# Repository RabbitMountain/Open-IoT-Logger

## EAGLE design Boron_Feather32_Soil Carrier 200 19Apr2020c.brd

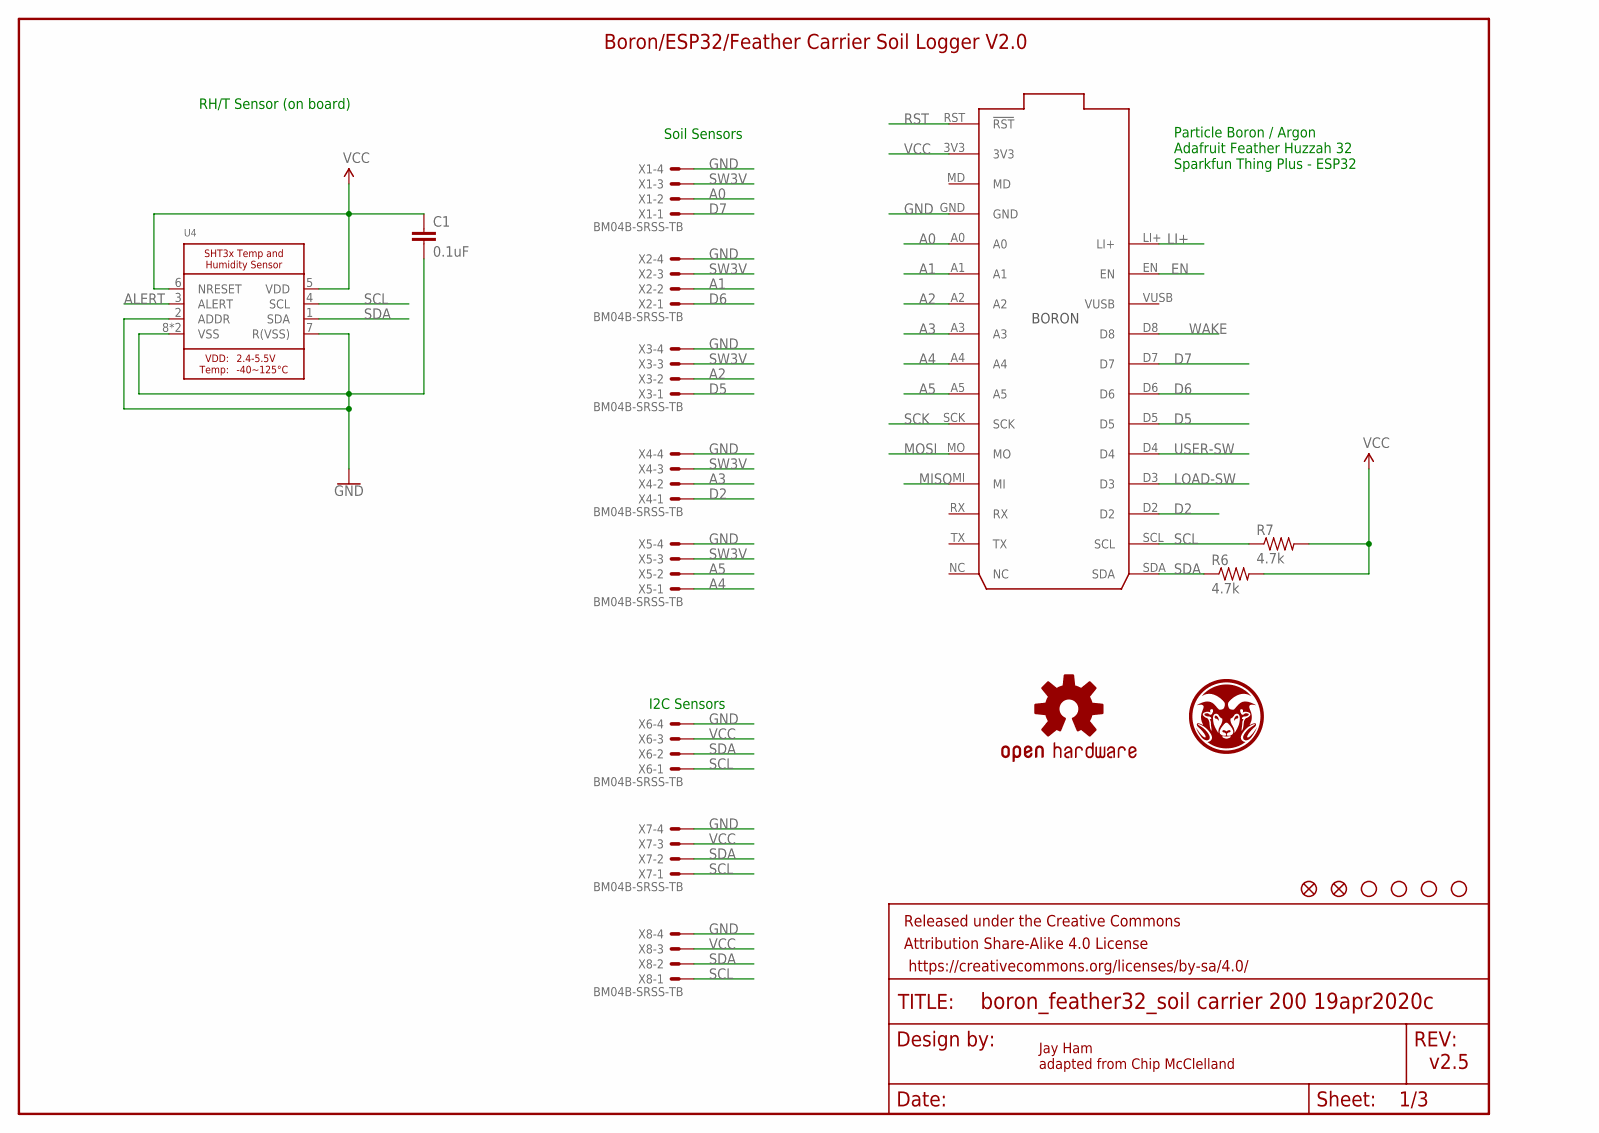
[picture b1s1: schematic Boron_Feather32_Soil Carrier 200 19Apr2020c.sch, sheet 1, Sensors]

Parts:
BORON: PARTICLE-DEVICES-BORON; PARTICLE-DEVICES_BORON
C1: 0.1uF; 0805
FD1, FD2: FIDUCIALUFIDUCIAL; FIDUCIAL-MICRO
FRAME1: FRAME-LETTER; CREATIVE_COMMONS
JP10, JP11, JP12, JP13: STAND-OFF
LOGO1: OSHW-LOGOM; OSHW-LOGO-M
R6, R7: 4.7k; 0805
U4: MICROBUILDER_SHT3X
U$1: CSU-RAM-LOGO7MM; CSU-RAM-7MM
X1, X2, X3, X4, X5, X6, X7, X8: BM04B-SRSS-TB

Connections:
A0: BORON.A0, X1.2
A1: BORON.A1, X2.2
A2: BORON.A2, X3.2
A3: BORON.A3, X4.2
A4: BORON.A4, X5.1
A5: BORON.A5, X5.2
ALERT: U4.3 (ALERT)
D2: BORON.D2, X4.1
D5: BORON.D5, X3.1
D6: BORON.D6, X2.1
D7: BORON.D7, X1.1
EN: BORON.EN; also elsewhere on the board
GND: BORON.GND, C1.2, U4.2 (ADDR), U4.7 (R(VSS)), U4.8 (VSS), U4.THERMAL (VSS), X1.4, X2.4, X3.4, X4.4, X5.4, X6.4, X7.4, X8.4; also elsewhere on the board
LI+: BORON.LI+; also elsewhere on the board
LOAD-SW: BORON.D3; also elsewhere on the board
MISO: BORON.MI
MOSI: BORON.MO
RST: BORON.RST (!RST); also elsewhere on the board
SCK: BORON.SCK
SCL: BORON.SCL, R7.1, U4.4 (SCL), X6.1, X7.1, X8.1; also elsewhere on the board
SDA: BORON.SDA, R6.1, U4.1 (SDA), X6.2, X7.2, X8.2; also elsewhere on the board
SW3V: X1.3, X2.3, X3.3, X4.3, X5.3; also elsewhere on the board
USER-SW: BORON.D4; also elsewhere on the board
VCC: BORON.3V3, C1.1, R6.2, R7.2, U4.5 (VDD), U4.6 (NRESET), X6.3, X7.3, X8.3; also elsewhere on the board
WAKE: BORON.D8; also elsewhere on the board

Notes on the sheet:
Jay Ham adapted from Chip McClelland
v2.5
Boron/ESP32/Feather Carrier Soil Logger V2.0
RH/T Sensor (on board)
I2C Sensors
Soil Sensors
Particle Boron / Argon Adafruit Feather Huzzah 32 Sparkfun Thing Plus - ESP32

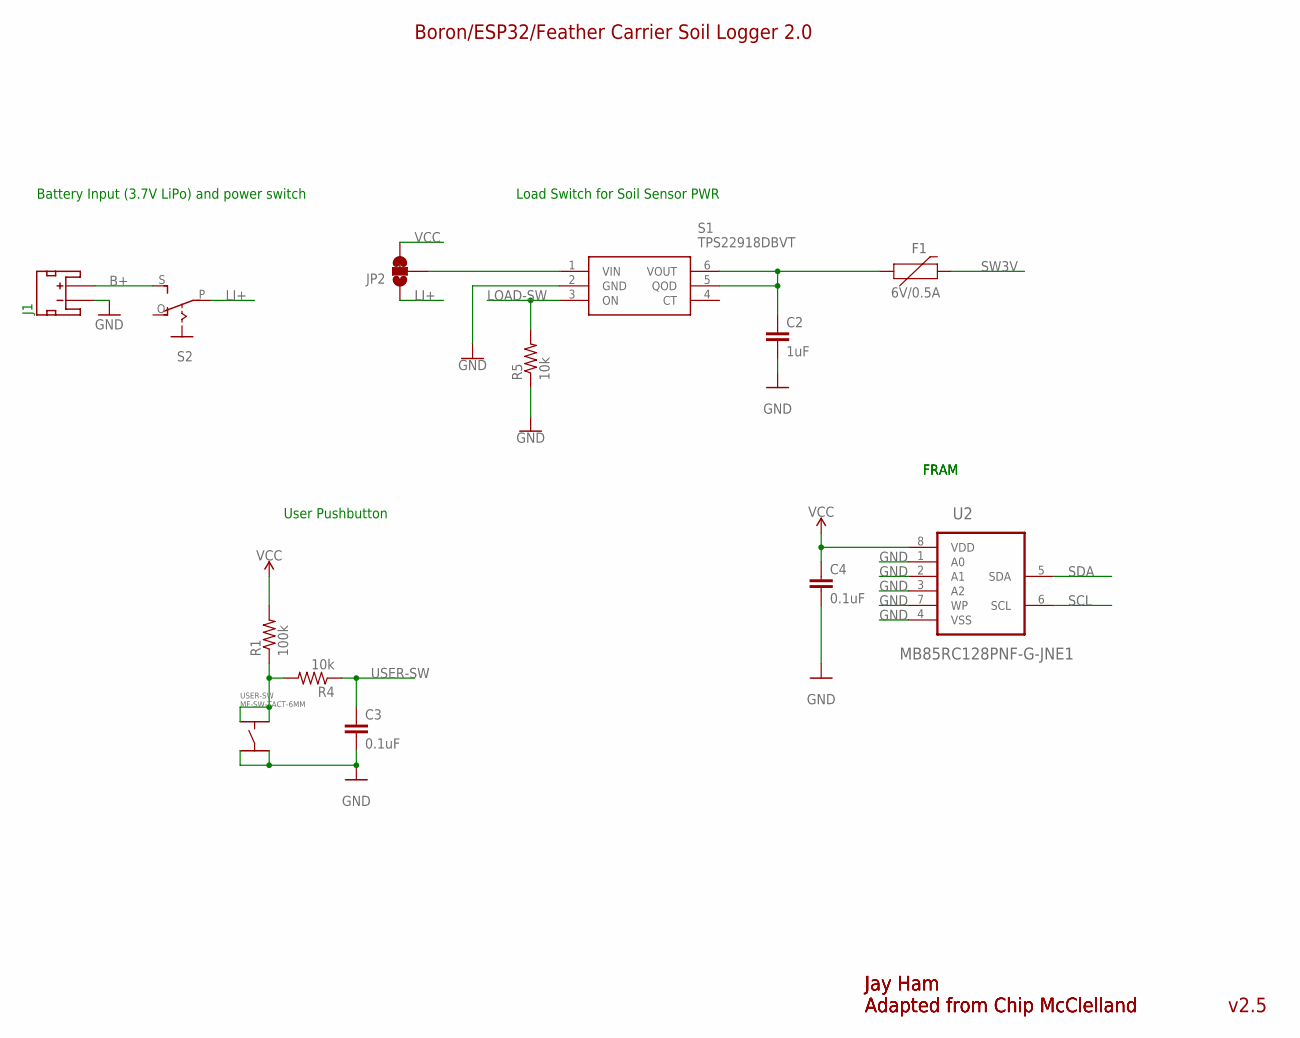
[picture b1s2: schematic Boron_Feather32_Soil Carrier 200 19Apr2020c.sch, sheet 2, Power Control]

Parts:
C2: 1uF; 0805
C3, C4: 0.1uF; 0805
F1: 6V/0.5A; 1206
J1: S2B-PH-SM4-TB(LF)(SN); JST-2-SMD
JP2: JUMPER-SMT_3_1-NC_TRACE_NO-SILK; SMT-JUMPER_3_1-NC_TRACE_NO-SILK
R1: 100k; 0805
R4, R5: 10k; 0805
S1: TPS22918DBVT; SOT95P280X145-6N
S2: EG1218S; EG1218
U2: MB85RC128PNF-G-JNE1; FUJITSU_BY_ELEMENT14_BATCH_1_SOIC127P600X175-8N
USER-SW: MF-SW-TACT-6MM; MF_SWITCHES_TACT6MM

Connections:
B+: J1.2 (+), S2.S; also elsewhere on the board
GND: C2.2, C3.2, C4.2, J1.1 (-), R5.1, S1.2 (GND), U2.1 (A0), U2.2 (A1), U2.3 (A2), U2.4 (VSS), U2.7 (WP), USER-SW.P$3, USER-SW.P$4; also elsewhere on the board
LI+: JP2.1, S2.P; also elsewhere on the board
LOAD-SW: R5.2, S1.3 (ON); also elsewhere on the board
unnamed: JP2.2, S1.1 (VIN)
unnamed: R1.1, R4.2, USER-SW.P$1, USER-SW.P$2
unnamed: C2.1, F1.1, S1.5 (QOD), S1.6 (VOUT)
SCL: U2.6 (SCL); also elsewhere on the board
SDA: U2.5 (SDA); also elsewhere on the board
SW3V: F1.2; also elsewhere on the board
USER-SW: C3.1, R4.1; also elsewhere on the board
VCC: C4.1, JP2.3, R1.2, U2.8 (VDD); also elsewhere on the board

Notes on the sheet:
Jay Ham Adapted from Chip McClelland
v2.5
Boron/ESP32/Feather Carrier Soil Logger 2.0
Load Switch for Soil Sensor PWR
Battery Input (3.7V LiPo) and power switch
FRAM
User Pushbutton

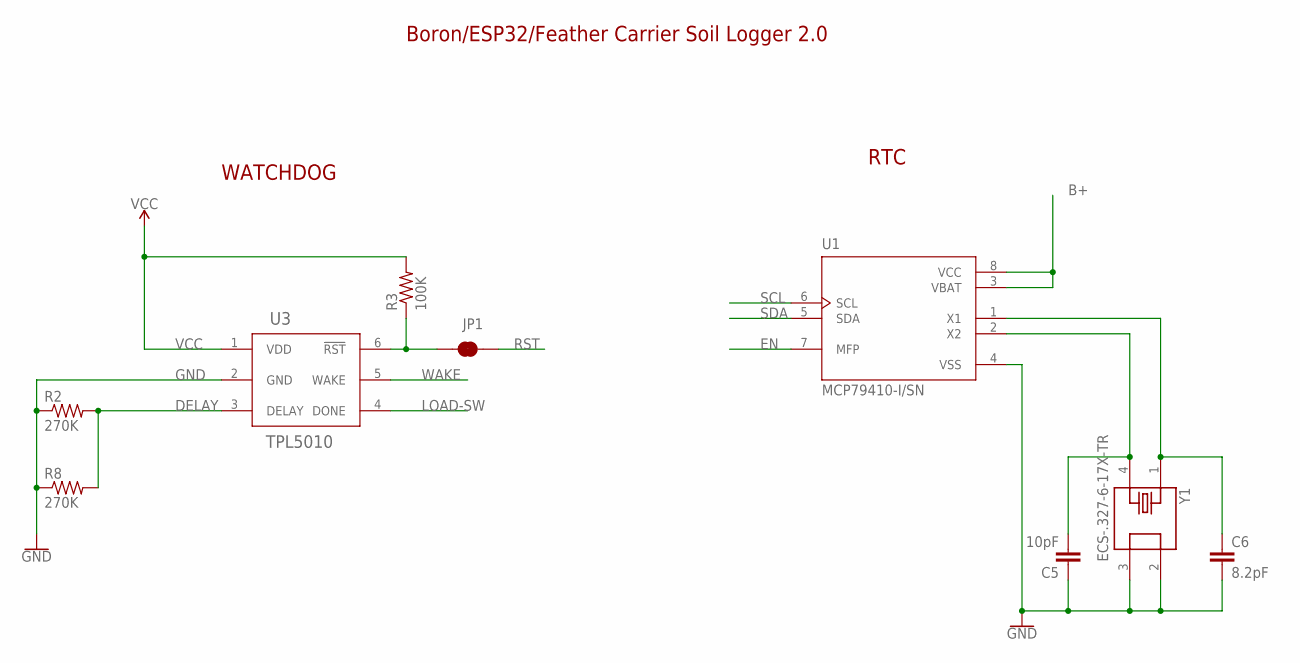
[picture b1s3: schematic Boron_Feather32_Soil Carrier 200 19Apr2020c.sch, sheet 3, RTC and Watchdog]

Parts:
C5: 10pF; SPARKFUN-CAPACITORS_0805$1
C6: 8.2pF; SPARKFUN-CAPACITORS_0805$1
JP1: JUMPER-SMT_2_NC_TRACE_NO-SILK; SMT-JUMPER_2_NC_TRACE_NO-SILK
R2, R8: 270K; SPARKFUN-PASSIVES_0805
R3: 100K; SPARKFUN-PASSIVES_0805
U1: MCP79410-I/SN; SOIC127P600X175-8N
U3: TPL5010; CUSTOM-COMPONENTS_TSOT-23
Y1: ECS-.327-6-17X-TR; CUSTOM-COMPONENTS_XTAL_ECS-.327-6-17X-TR

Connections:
B+: U1.3 (VBAT), U1.8 (VCC); also elsewhere on the board
DELAY: R2.2, R8.2, U3.3 (DELAY)
EN: U1.7 (MFP); also elsewhere on the board
GND: C5.1, C6.2, R2.1, R8.1, U1.4 (VSS), U3.2 (GND), Y1.2, Y1.3; also elsewhere on the board
LOAD-SW: U3.4 (DONE); also elsewhere on the board
unnamed: C5.2, U1.2 (X2), Y1.4
unnamed: C6.1, U1.1 (X1), Y1.1
unnamed: JP1.2, R3.1, U3.6 (!RST)
RST: JP1.1; also elsewhere on the board
SCL: U1.6 (SCL); also elsewhere on the board
SDA: U1.5 (SDA); also elsewhere on the board
VCC: R3.2, U3.1 (VDD); also elsewhere on the board
WAKE: U3.5 (WAKE); also elsewhere on the board

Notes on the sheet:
Boron/ESP32/Feather Carrier Soil Logger 2.0
RTC
WATCHDOG

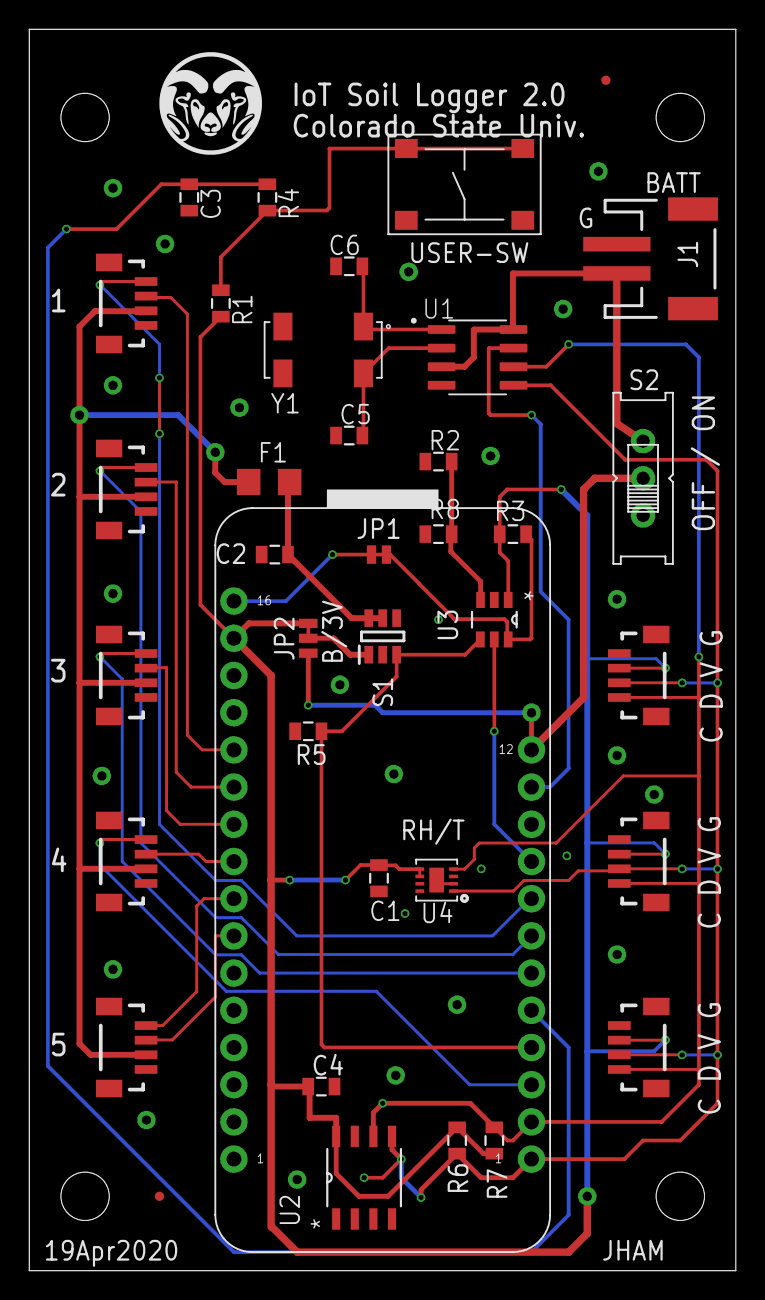
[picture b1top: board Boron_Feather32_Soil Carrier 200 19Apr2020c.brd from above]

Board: 2 copper layers, 48.2 x 84.8 mm, 44 parts (1 on the bottom side), 29 nets.

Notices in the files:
parts and their libraries:
SparkFun-Passives: Licensing: Creative Commons ShareAlike 4.0 International - https://creativecommons.org/licenses/by-sa/4.0
SparkFun-Aesthetics: Released under the Creative Commons Attribution Share-Alike 4.0 License
SparkFun-Aesthetics: https://creativecommons.org/licenses/by-sa/4.0
